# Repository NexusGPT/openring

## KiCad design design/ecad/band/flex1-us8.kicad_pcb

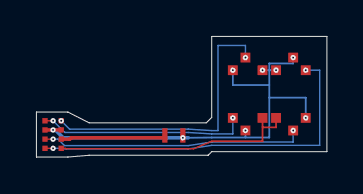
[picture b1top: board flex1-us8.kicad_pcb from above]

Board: 2 copper layers, 16.1 x 6.7 mm, 7 parts (0 on the bottom side), 7 nets.

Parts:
J_BAND_A: J_BAND_A_TAIL
M1: W0525AB001D_Lands
SW1, SW3, SW4, SW5: Alps_SKTAAAE010_pads34
SW2: Alps_SKTAAAE010_4pad

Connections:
BTN_REC: J_BAND_A.5, SW2.1, SW2.3
GND: J_BAND_A.6, J_BAND_A.8, M1.2, SW1.4, SW2.2, SW2.4, SW3.4, SW4.4, SW5.4
JOY_DOWN: J_BAND_A.2, SW3.3
JOY_LEFT: J_BAND_A.3, SW4.3
JOY_RIGHT: J_BAND_A.4, SW5.3
JOY_UP: J_BAND_A.1, SW1.3
VMOT: J_BAND_A.7, M1.1

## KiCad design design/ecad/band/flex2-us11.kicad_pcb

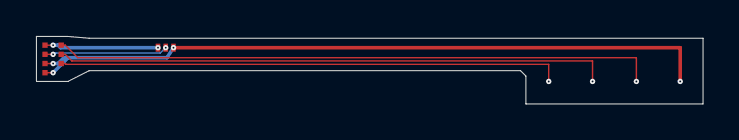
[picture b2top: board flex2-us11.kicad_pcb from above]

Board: 2 copper layers, 37.0 x 3.8 mm, 6 parts (0 on the bottom side), 6 nets.

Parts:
CP1, CP2, CP3, CP4: CP_Pad_1.6
J_BAND_B: J_BAND_B_TAIL
PRT1: PRT1_Tabs

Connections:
GND: CP4.1, J_BAND_B.2, J_BAND_B.7, PRT1.2
NTC: J_BAND_B.3, PRT1.3
USB_DN: CP2.1, J_BAND_B.5
USB_DP: CP3.1, J_BAND_B.6
VBAT: J_BAND_B.1, PRT1.1
VBUS: CP1.1, J_BAND_B.4

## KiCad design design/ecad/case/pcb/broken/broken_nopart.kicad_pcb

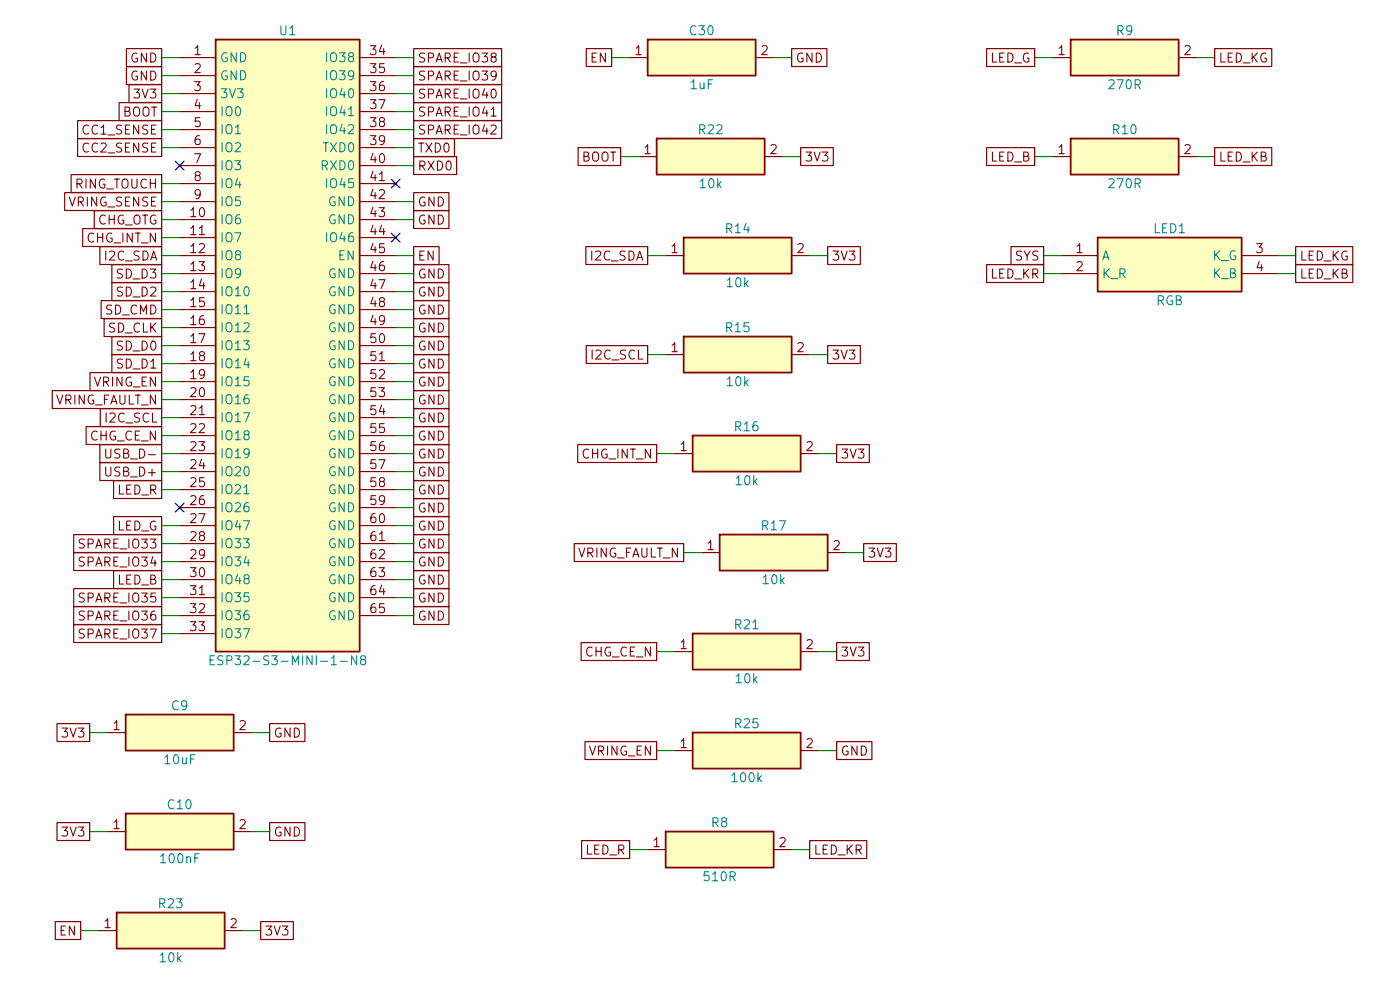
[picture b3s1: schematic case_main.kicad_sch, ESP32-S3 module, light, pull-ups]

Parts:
C9: 10uF; MPN GRM188R60J106ME47D
C10: 100nF; MPN GRM155R71C104KA88D
C30: 1uF; MPN GRM155R61A105KE15D
LED1: RGB; MPN APTF1616SEEZGQBDC
R8: 510R; MPN RC0402FR-07510RL
R9, R10: 270R; MPN RC0402FR-07270RL
R14, R15, R16, R17, R21, R22, R23: 10k; MPN RC0402FR-0710KL
R25: 100k; MPN RC0402FR-07100KL
U1: ESP32-S3-MINI-1-N8; MPN ESP32-S3-MINI-1-N8

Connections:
3V3: C9.1, C10.1, R14.2, R15.2, R16.2, R17.2, R21.2, R22.2, R23.2, U1.3 (3V3); also elsewhere on the board
BOOT: R22.1, U1.4 (IO0); also elsewhere on the board
CC1_SENSE: U1.5 (IO1); also elsewhere on the board
CC2_SENSE: U1.6 (IO2); also elsewhere on the board
CHG_CE_N: R21.1, U1.22 (IO18); also elsewhere on the board
CHG_INT_N: R16.1, U1.11 (IO7); also elsewhere on the board
CHG_OTG: U1.10 (IO6); also elsewhere on the board
EN: C30.1, R23.1, U1.45 (EN); also elsewhere on the board
GND: C9.2, C10.2, C30.2, R25.2, U1.1 (GND), U1.2 (GND), U1.42 (GND), U1.43 (GND), U1.46 (GND), U1.47 (GND), U1.48 (GND), U1.49 (GND), U1.50 (GND), U1.51 (GND), U1.52 (GND), U1.53 (GND), U1.54 (GND), U1.55 (GND), U1.56 (GND), U1.57 (GND), U1.58 (GND), U1.59 (GND), U1.60 (GND), U1.61 (GND), U1.62 (GND), U1.63 (GND), U1.64 (GND), U1.65 (GND); also elsewhere on the board
I2C_SCL: R15.1, U1.21 (IO17); also elsewhere on the board
I2C_SDA: R14.1, U1.12 (IO8); also elsewhere on the board
LED_B: R10.1, U1.30 (IO48)
LED_G: R9.1, U1.27 (IO47)
LED_KB: LED1.4 (K_B), R10.2
LED_KG: LED1.3 (K_G), R9.2
LED_KR: LED1.2 (K_R), R8.2
LED_R: R8.1, U1.25 (IO21)
RING_TOUCH: U1.8 (IO4); also elsewhere on the board
RXD0: U1.40 (RXD0); also elsewhere on the board
SD_CLK: U1.16 (IO12); also elsewhere on the board
SD_CMD: U1.15 (IO11); also elsewhere on the board
SD_D0: U1.17 (IO13); also elsewhere on the board
SD_D1: U1.18 (IO14); also elsewhere on the board
SD_D2: U1.14 (IO10); also elsewhere on the board
SD_D3: U1.13 (IO9); also elsewhere on the board
SPARE_IO33: U1.28 (IO33); also elsewhere on the board
SPARE_IO34: U1.29 (IO34); also elsewhere on the board
SPARE_IO35: U1.31 (IO35); also elsewhere on the board
SPARE_IO36: U1.32 (IO36); also elsewhere on the board
SPARE_IO37: U1.33 (IO37); also elsewhere on the board
SPARE_IO38: U1.34 (IO38); also elsewhere on the board
SPARE_IO39: U1.35 (IO39); also elsewhere on the board
SPARE_IO40: U1.36 (IO40); also elsewhere on the board
SPARE_IO41: U1.37 (IO41); also elsewhere on the board
SPARE_IO42: U1.38 (IO42); also elsewhere on the board
SYS: LED1.1 (A); also elsewhere on the board
TXD0: U1.39 (TXD0); also elsewhere on the board
USB_D+: U1.24 (IO20); also elsewhere on the board
USB_D-: U1.23 (IO19); also elsewhere on the board
VRING_EN: R25.1, U1.19 (IO15); also elsewhere on the board
VRING_FAULT_N: R17.1, U1.20 (IO16); also elsewhere on the board
VRING_SENSE: U1.9 (IO5); also elsewhere on the board

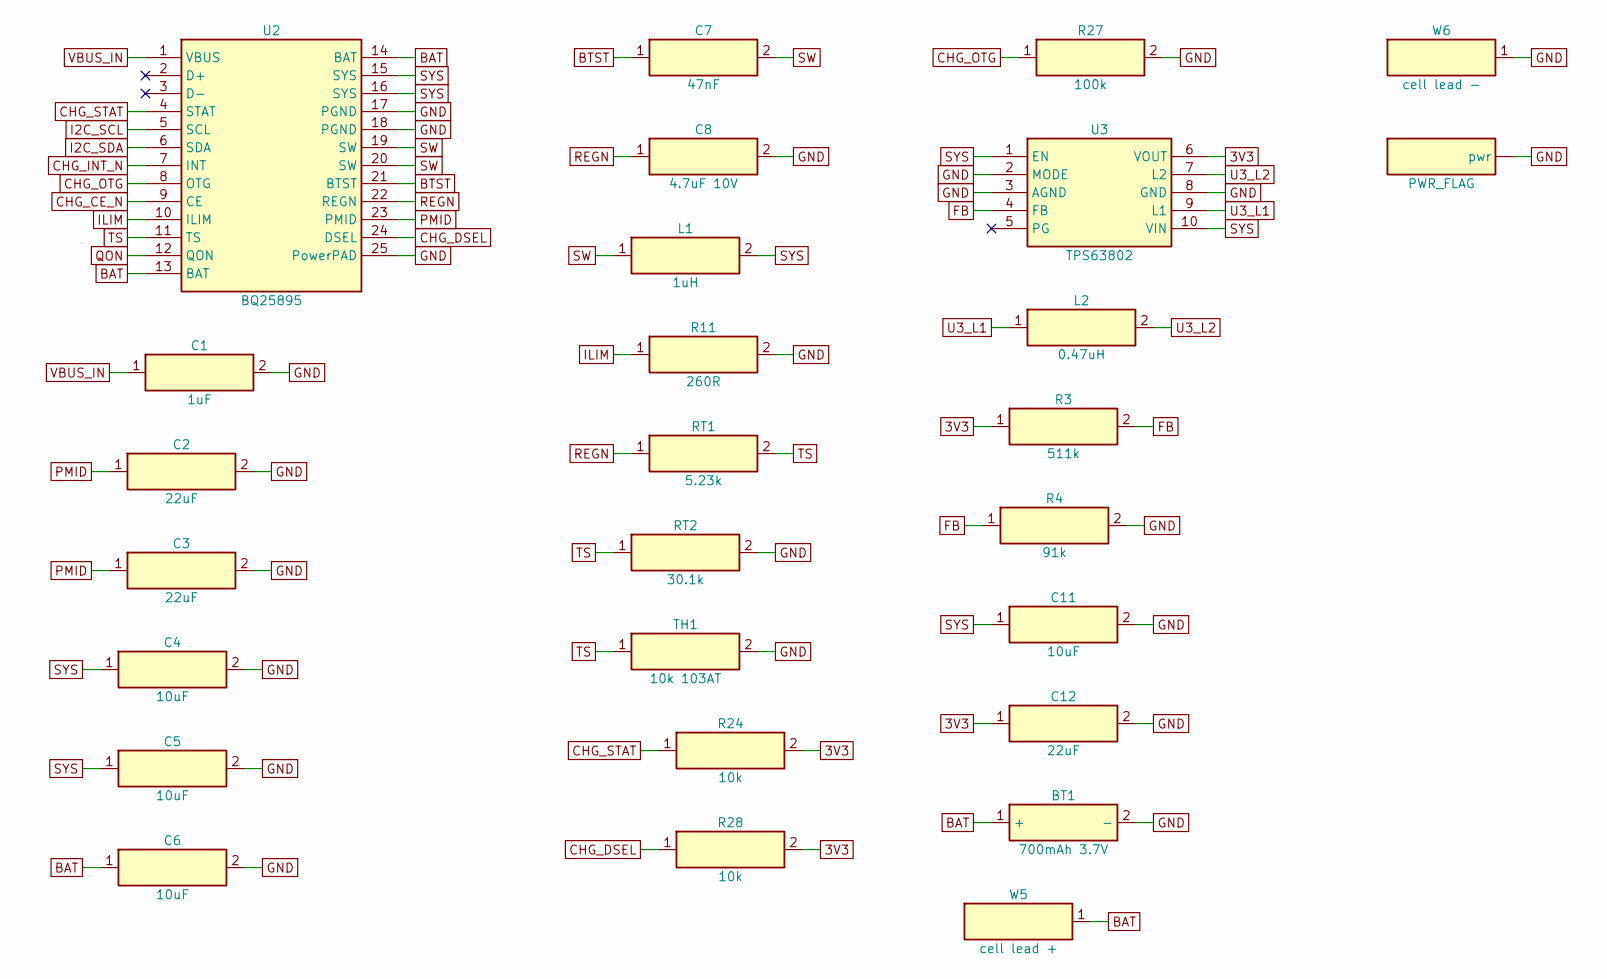
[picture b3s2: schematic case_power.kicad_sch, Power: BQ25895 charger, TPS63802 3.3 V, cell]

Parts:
BT1: 700mAh 3.7V; MPN DNK852338
C1: 1uF; MPN GRM188R61A105KA61D
C2, C3: 22uF; MPN GRM21BR61A226ME44L
C4, C5, C6, C11: 10uF; MPN GRM188R61A106KE69D
C7: 47nF; MPN GRM155R71C473KA01D
C8: 4.7uF 10V; MPN GRM188R61A475KE15D
C12: 22uF; MPN GRM188R60J226MEA0D
L1: 1uH; MPN XFL4020-102MEC
L2: 0.47uH; MPN XFL4015-471MEC
R3: 511k; MPN RC0402FR-07511KL
R4: 91k; MPN RC0402FR-0791KL
R11: 260R; MPN RC0402FR-07261RL
R24, R28: 10k; MPN RC0402FR-0710KL
R27: 100k; MPN RC0402FR-07100KL
RT1: 5.23k; MPN RC0402FR-075K23L
RT2: 30.1k; MPN RC0402FR-0730K1L
TH1: 10k 103AT; MPN 103AT-2
U2: BQ25895; MPN BQ25895RTWR
U3: TPS63802; MPN TPS63802DLAR
W5: cell lead +
W6: cell lead -

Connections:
3V3: C12.1, R3.1, R24.2, R28.2, U3.6 (VOUT); also elsewhere on the board
BAT: BT1.1 (+), C6.1, U2.13 (BAT), U2.14 (BAT), W5.1
BTST: C7.1, U2.21 (BTST)
CHG_CE_N: U2.9 (CE); also elsewhere on the board
CHG_DSEL: R28.1, U2.24 (DSEL)
CHG_INT_N: U2.7 (INT); also elsewhere on the board
CHG_OTG: R27.1, U2.8 (OTG); also elsewhere on the board
CHG_STAT: R24.1, U2.4 (STAT)
FB: R3.2, R4.1, U3.4 (FB)
GND: BT1.2 (-), C1.2, C2.2, C3.2, C4.2, C5.2, C6.2, C8.2, C11.2, C12.2, R4.2, R11.2, R27.2, RT2.2, TH1.2, U2.17 (PGND), U2.18 (PGND), U2.25 (PowerPAD), U3.2 (MODE), U3.3 (AGND), U3.8 (GND), W6.1; also elsewhere on the board
I2C_SCL: U2.5 (SCL); also elsewhere on the board
I2C_SDA: U2.6 (SDA); also elsewhere on the board
ILIM: R11.1, U2.10 (ILIM)
PMID: C2.1, C3.1, U2.23 (PMID); also elsewhere on the board
QON: U2.12 (QON); also elsewhere on the board
REGN: C8.1, RT1.1, U2.22 (REGN)
SW: C7.2, L1.1, U2.19 (SW), U2.20 (SW)
SYS: C4.1, C5.1, C11.1, L1.2, U2.15 (SYS), U2.16 (SYS), U3.1 (EN), U3.10 (VIN); also elsewhere on the board
TS: RT1.2, RT2.1, TH1.1, U2.11 (TS)
U3_L1: L2.1, U3.9 (L1)
U3_L2: L2.2, U3.7 (L2)
VBUS_IN: C1.1, U2.1 (VBUS); also elsewhere on the board

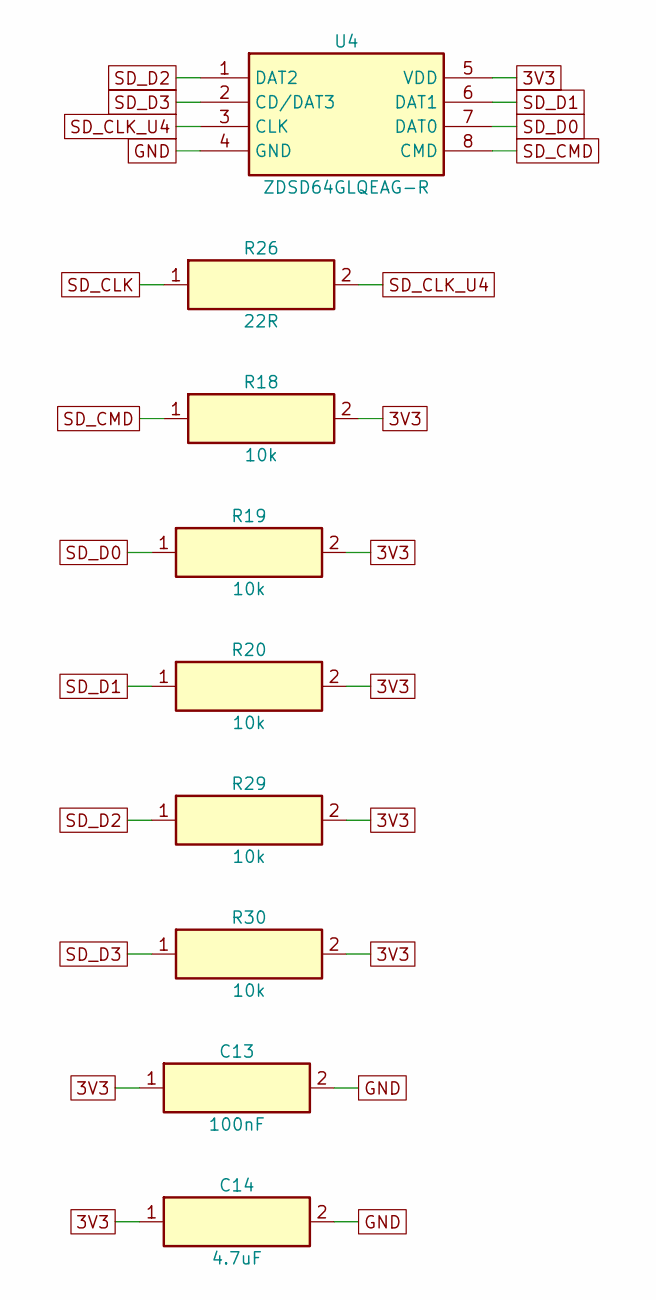
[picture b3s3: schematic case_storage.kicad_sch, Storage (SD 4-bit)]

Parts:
C13: 100nF; MPN GRM155R71C104KA88D
C14: 4.7uF; MPN GRM188R61A475KE15D
R18, R19, R20, R29, R30: 10k; MPN RC0402FR-0710KL
R26: 22R; MPN RC0402FR-0722RL
U4: ZDSD64GLQEAG-R; MPN ZDSD64GLQEAG-R

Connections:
3V3: C13.1, C14.1, R18.2, R19.2, R20.2, R29.2, R30.2, U4.5 (VDD); also elsewhere on the board
GND: C13.2, C14.2, U4.4 (GND); also elsewhere on the board
SD_CLK: R26.1; also elsewhere on the board
SD_CLK_U4: R26.2, U4.3 (CLK)
SD_CMD: R18.1, U4.8 (CMD); also elsewhere on the board
SD_D0: R19.1, U4.7 (DAT0); also elsewhere on the board
SD_D1: R20.1, U4.6 (DAT1); also elsewhere on the board
SD_D2: R29.1, U4.1 (DAT2); also elsewhere on the board
SD_D3: R30.1, U4.2 (CD/DAT3); also elsewhere on the board

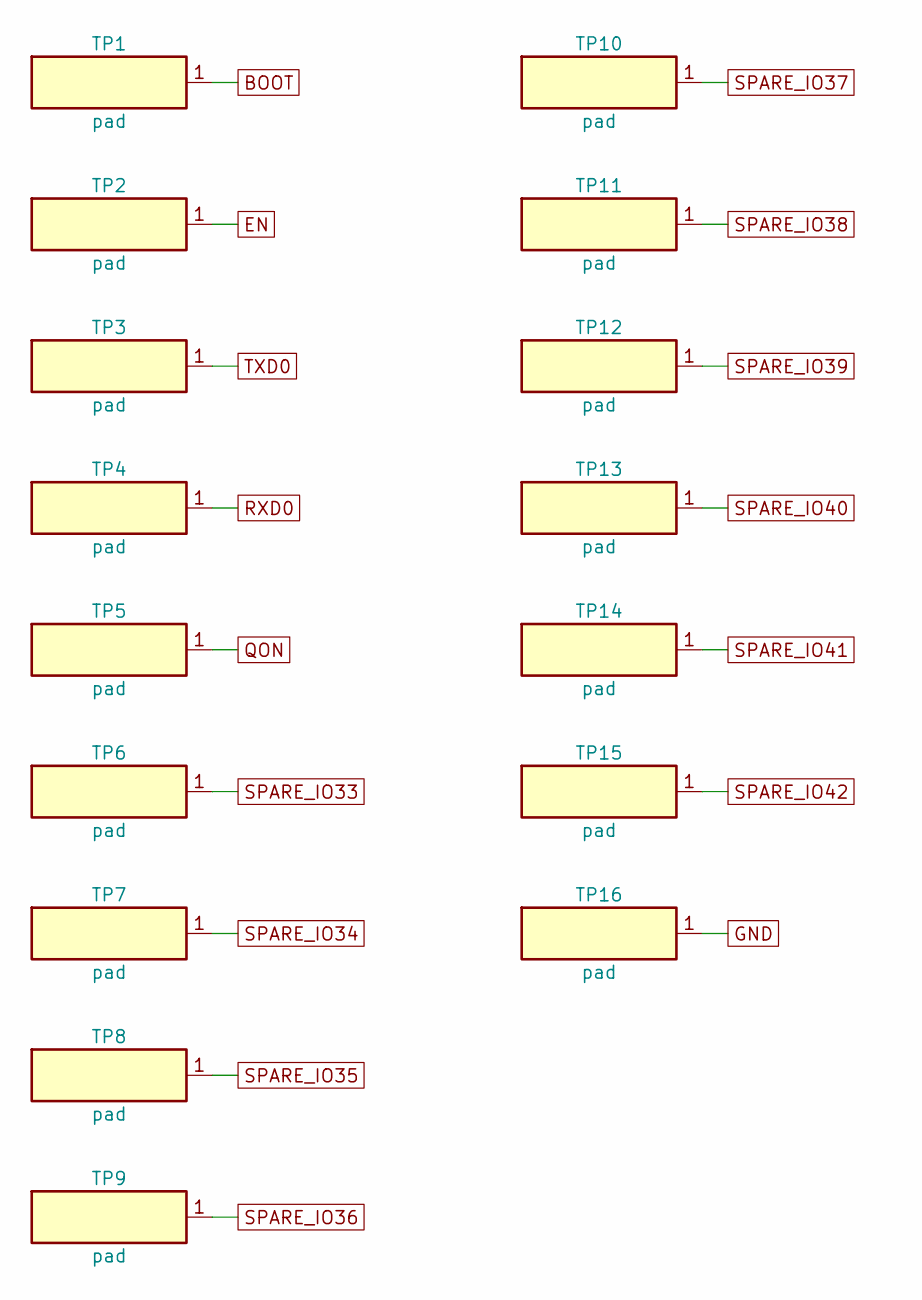
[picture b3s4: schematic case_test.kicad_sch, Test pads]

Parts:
TP1, TP2, TP3, TP4, TP5, TP6, TP7, TP8, TP9, TP10, TP11, TP12, TP13, TP14, TP15, TP16: pad

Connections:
BOOT: TP1.1; also elsewhere on the board
EN: TP2.1; also elsewhere on the board
GND: TP16.1; also elsewhere on the board
QON: TP5.1; also elsewhere on the board
RXD0: TP4.1; also elsewhere on the board
SPARE_IO33: TP6.1; also elsewhere on the board
SPARE_IO34: TP7.1; also elsewhere on the board
SPARE_IO35: TP8.1; also elsewhere on the board
SPARE_IO36: TP9.1; also elsewhere on the board
SPARE_IO37: TP10.1; also elsewhere on the board
SPARE_IO38: TP11.1; also elsewhere on the board
SPARE_IO39: TP12.1; also elsewhere on the board
SPARE_IO40: TP13.1; also elsewhere on the board
SPARE_IO41: TP14.1; also elsewhere on the board
SPARE_IO42: TP15.1; also elsewhere on the board
TXD0: TP3.1; also elsewhere on the board

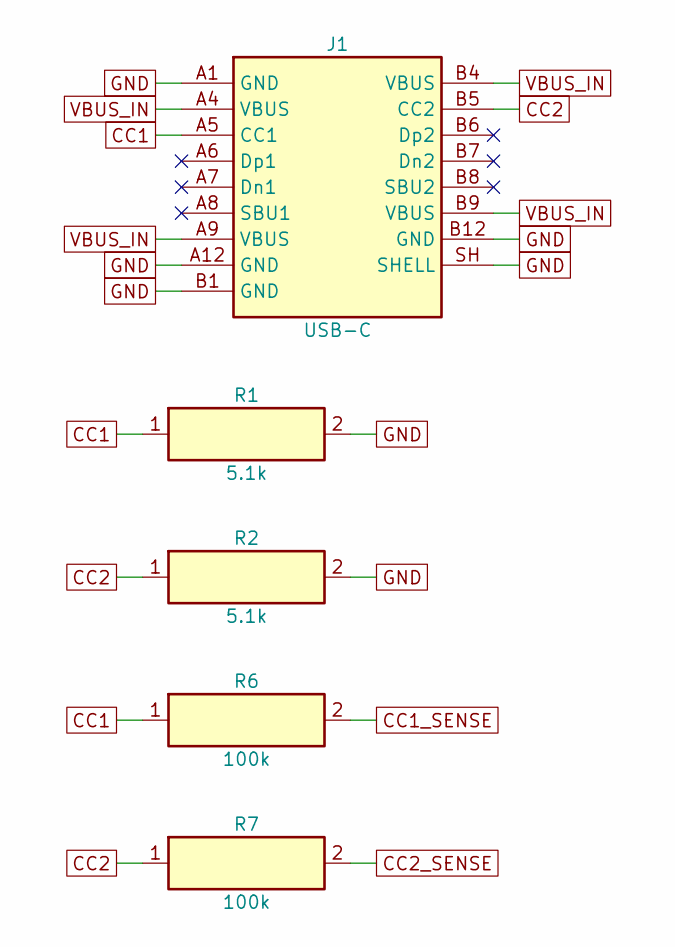
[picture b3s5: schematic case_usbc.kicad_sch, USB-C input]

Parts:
J1: USB-C; MPN USB4105-GF-A
R1, R2: 5.1k; MPN RC0402FR-075K1L
R6, R7: 100k; MPN RC0402FR-07100KL

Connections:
CC1: J1.A5 (CC1), R1.1, R6.1
CC1_SENSE: R6.2; also elsewhere on the board
CC2: J1.B5 (CC2), R2.1, R7.1
CC2_SENSE: R7.2; also elsewhere on the board
GND: J1.A1 (GND), J1.A12 (GND), J1.B1 (GND), J1.B12 (GND), J1.SH (SHELL), R1.2, R2.2; also elsewhere on the board
VBUS_IN: J1.A4 (VBUS), J1.A9 (VBUS), J1.B4 (VBUS), J1.B9 (VBUS); also elsewhere on the board

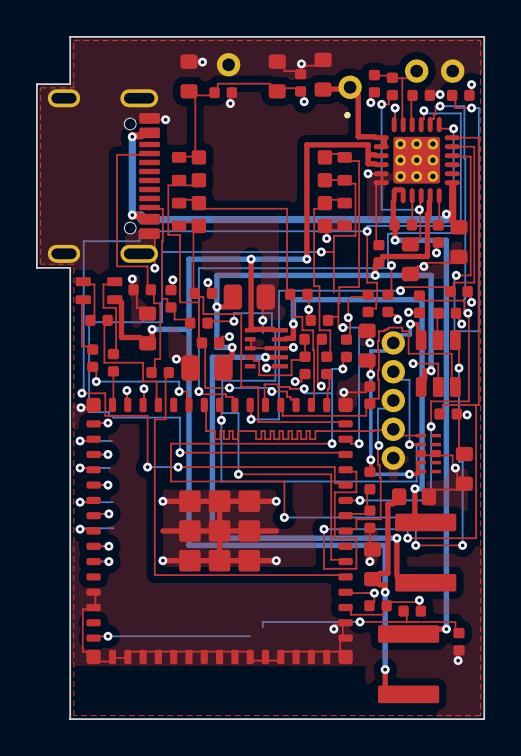
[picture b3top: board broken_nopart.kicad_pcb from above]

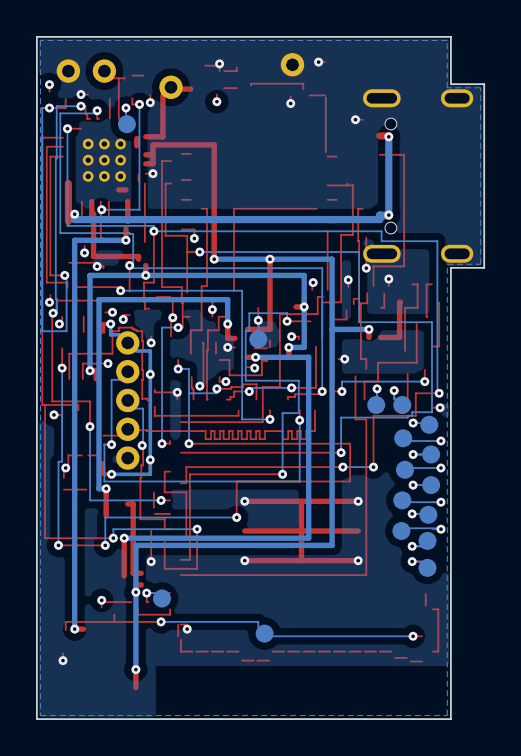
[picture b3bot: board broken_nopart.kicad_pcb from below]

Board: 4 copper layers, 24.8 x 37.9 mm, 83 parts (16 on the bottom side), 61 nets.

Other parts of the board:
C15: 10uF; SMD_0603
C16: 100nF; SMD_0402
R5: 59.0k; SMD_0402
R12: 100k; SMD_0402
R13: 47k; SMD_0402
U5: TPS2553; SOT-23-6_DBV
U6: TPD4E05U06; USON-10_DQA_1x2.5
W1, W2, W3, W4, W7: wire 30AWG; WIRE_PTH_0.7

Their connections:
GND: C15.2, C16.2, R5.2, R13.2, U5.2, U6.3, U6.8, W4.1; also elsewhere on the board
PMID: C16.1, U5.1; also elsewhere on the board
RING_TOUCH: W7.1; also elsewhere on the board
U5_ILIM: R5.1, U5.5
USB_D+: U6.1, W3.1; also elsewhere on the board
USB_D-: U6.2, W2.1; also elsewhere on the board
VRING: C15.1, R12.1, U5.6, U6.4, U6.5, W1.1
VRING_EN: U5.3; also elsewhere on the board
VRING_FAULT_N: U5.4; also elsewhere on the board
VRING_SENSE: R12.2, R13.1; also elsewhere on the board
